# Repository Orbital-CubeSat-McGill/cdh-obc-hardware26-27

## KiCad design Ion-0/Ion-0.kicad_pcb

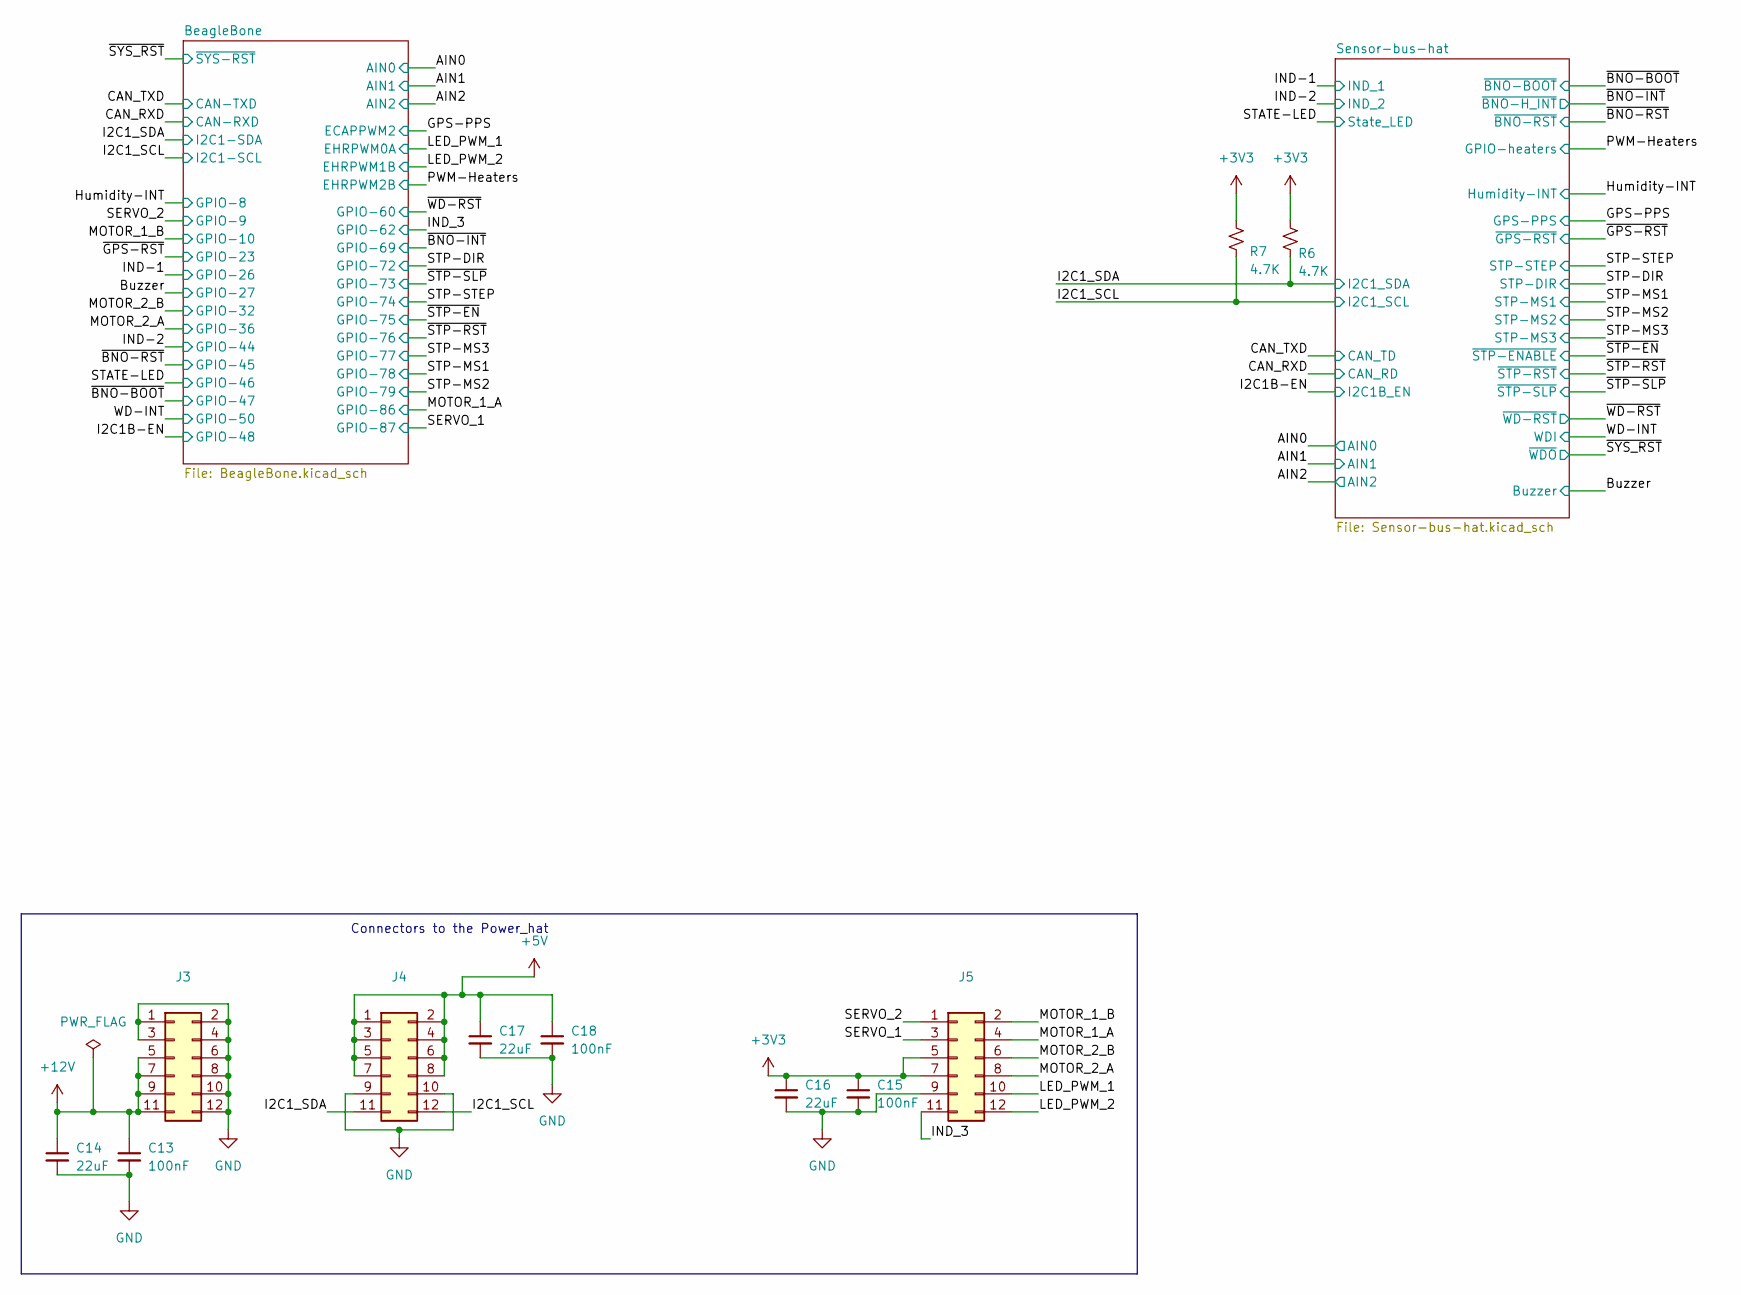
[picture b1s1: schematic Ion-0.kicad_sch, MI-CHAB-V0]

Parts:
C13, C15, C18: 100nF; C_0603_1608Metric
C14, C16, C17: 22uF; C_0603_1608Metric
J3, J4, J5: Conn_02x06_Odd_Even; PinSocket_2x06_P2.54mm_Vertical_SMD
R6, R7: 4.7K; R_0603_1608Metric_Pad0.98x0.95mm_HandSolder

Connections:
+3V3: C15.1, C16.1, J5.5, J5.7, R6.2, R7.1; also elsewhere on the board
+5V: C17.1, C18.1, J4.1, J4.2, J4.3, J4.4, J4.5, J4.6, J4.7, J4.8; also elsewhere on the board
+12V: C13.1, C14.1, J3.5, J3.7, J3.9, J3.11; also elsewhere on the board
/I2C1_SCL: J4.12, R7.2; also elsewhere on the board
/I2C1_SDA: J4.11, R6.1; also elsewhere on the board
/IND_3: J5.11; also elsewhere on the board
/LED_PWM_1: J5.10; also elsewhere on the board
/LED_PWM_2: J5.12; also elsewhere on the board
/MOTOR_1_A: J5.4; also elsewhere on the board
/MOTOR_1_B: J5.2; also elsewhere on the board
/MOTOR_2_A: J5.8; also elsewhere on the board
/MOTOR_2_B: J5.6; also elsewhere on the board
/SERVO_1: J5.3; also elsewhere on the board
/SERVO_2: J5.1; also elsewhere on the board
GND: C13.2, C14.2, C15.2, C16.2, C17.2, C18.2, J3.1, J3.2, J3.3, J3.4, J3.6, J3.8, J3.10, J3.12, J4.9, J4.10, J5.9; also elsewhere on the board

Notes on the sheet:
Connectors to the Power_hat

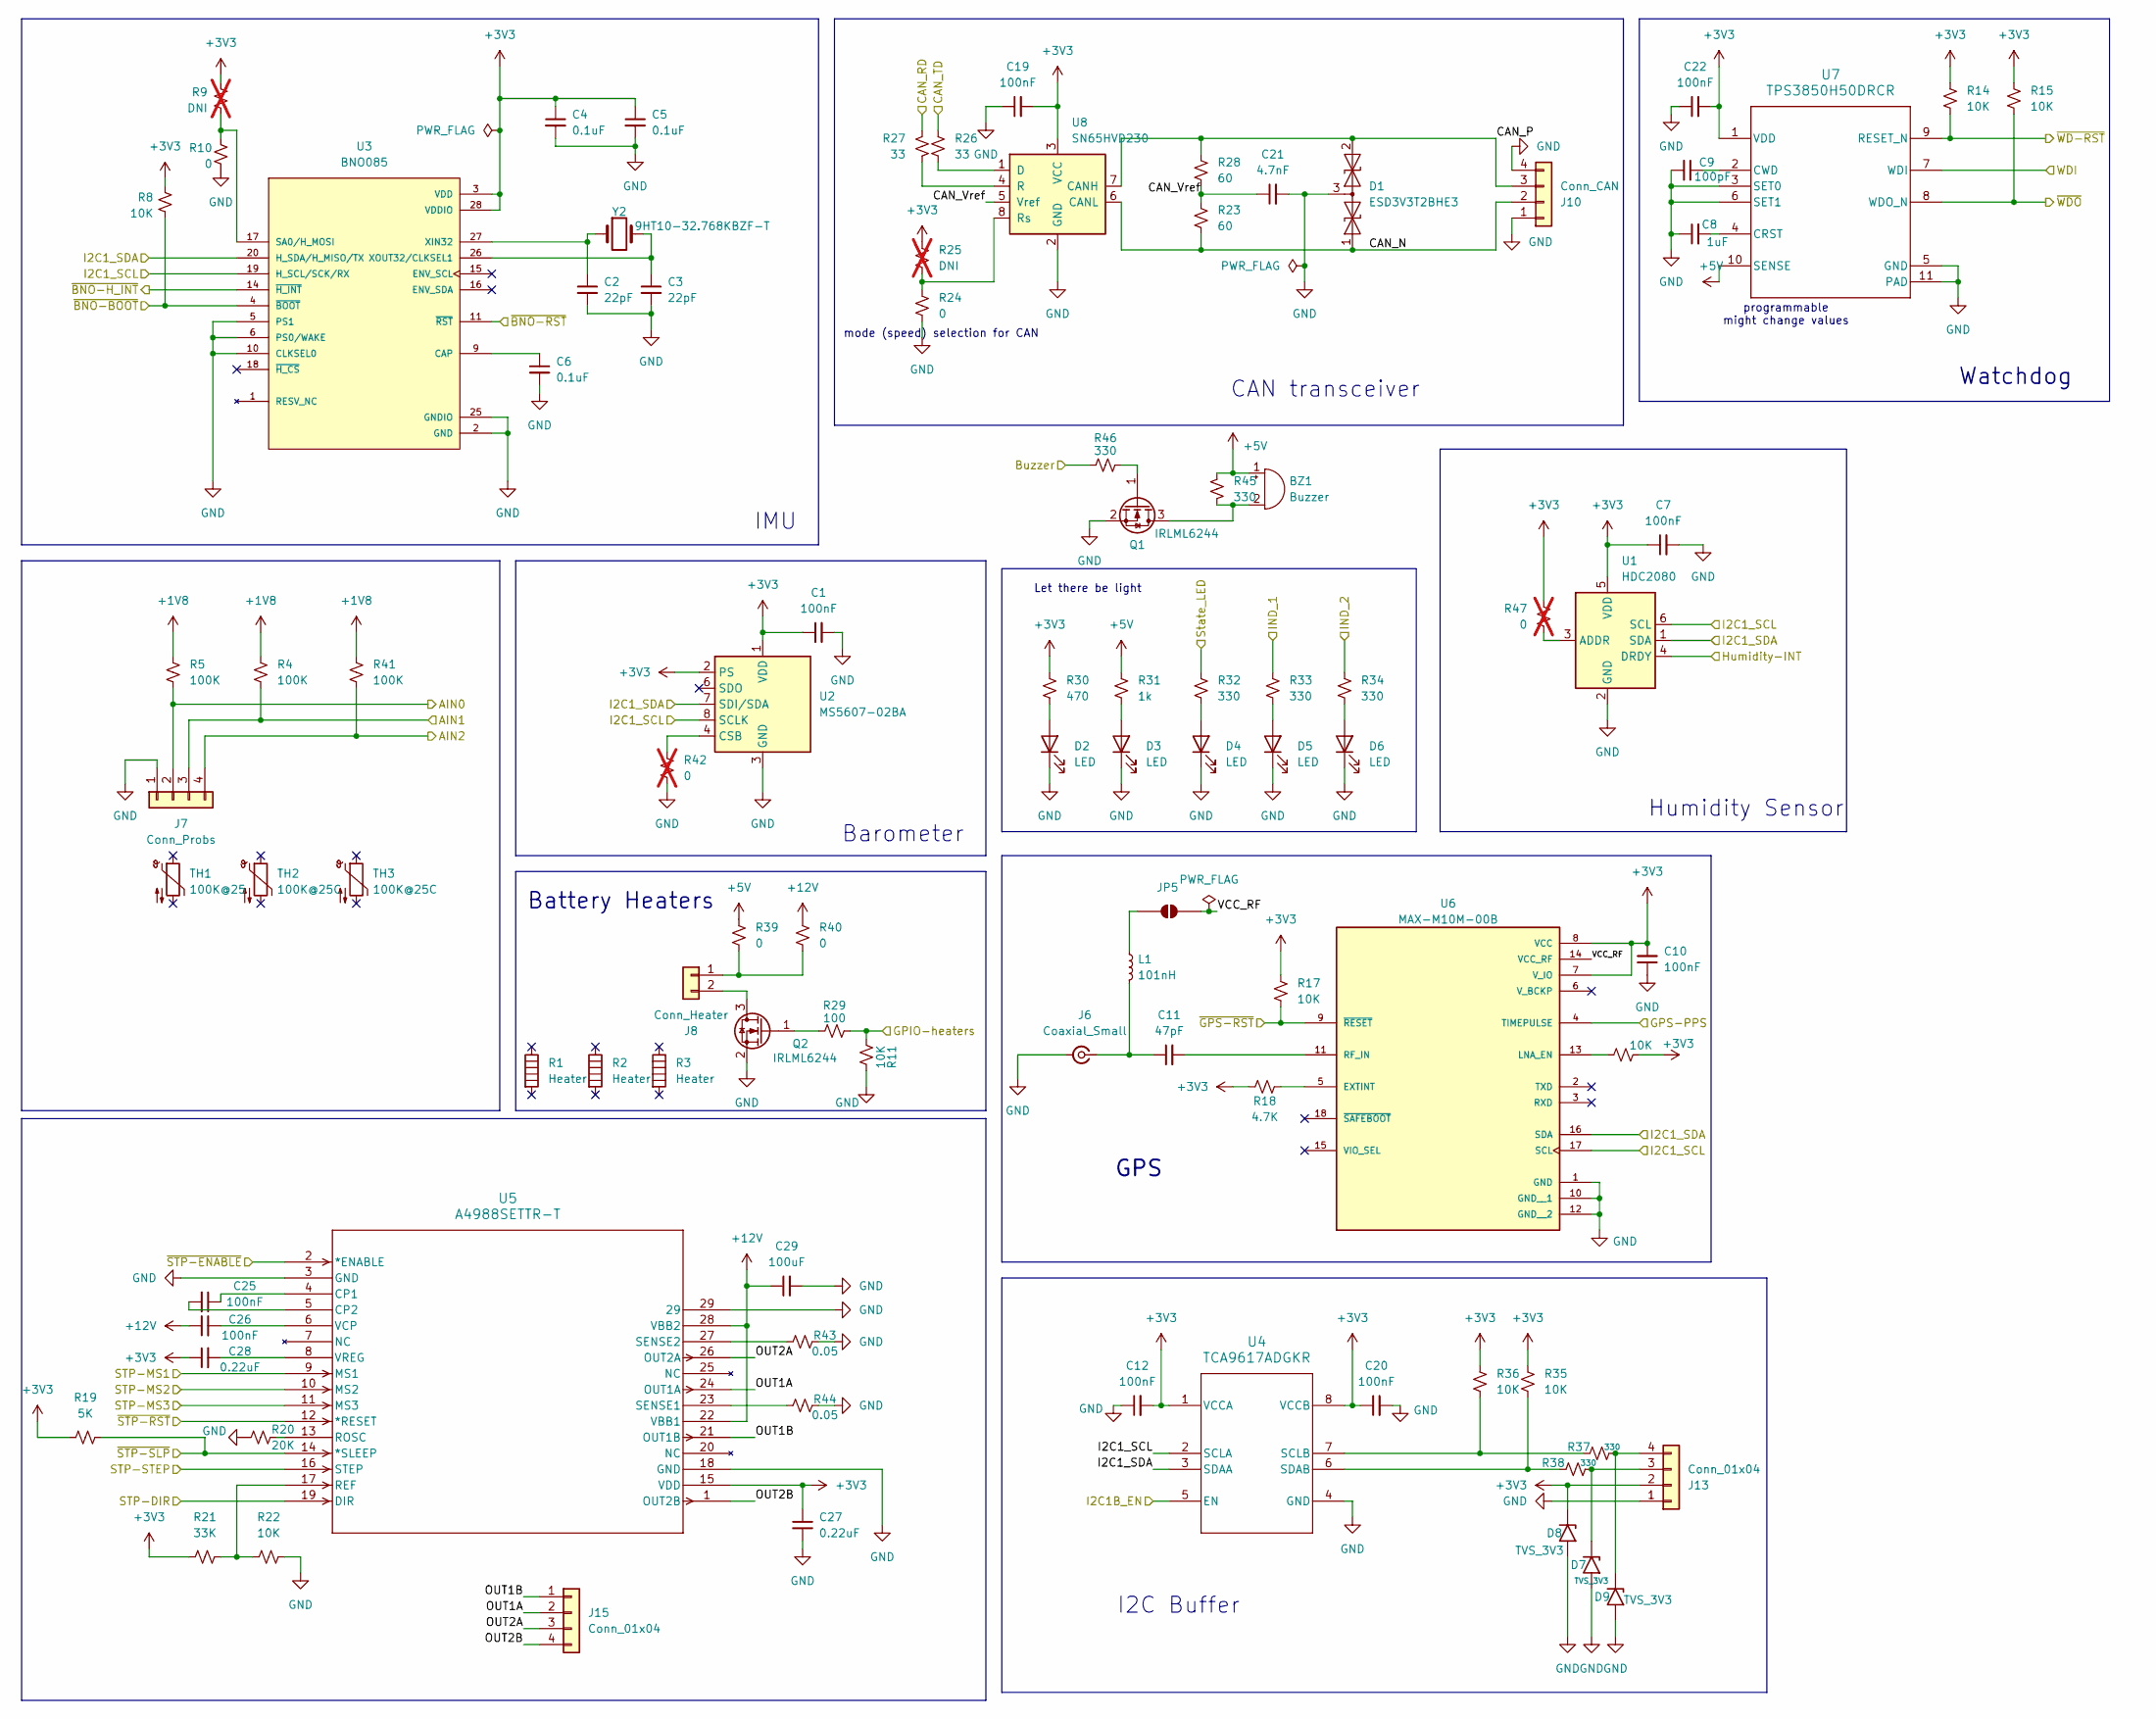
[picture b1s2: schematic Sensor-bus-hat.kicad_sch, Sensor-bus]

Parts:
BZ1: Buzzer; Buzzer_CUI_CPT-9019S-SMT
C1, C7, C10, C12, C19, C20, C22, C25, C26: 100nF; C_0603_1608Metric
C2, C3: 22pF; C_0603_1608Metric
C4, C5, C6: 0.1uF; C_0603_1608Metric
C8: 1uF; C_0603_1608Metric
C9: 100pF; C_0603_1608Metric
C11: 47pF; C_0402_1005Metric
C21: 4.7nF; C_0603_1608Metric
C27, C28: 0.22uF; C_0603_1608Metric
C29: 100uF; C_0603_1608Metric
D1: ESD3V3T2BHE3; SOT-23
D2, D3, D4, D5, D6: LED; LED_0603_1608Metric_Pad1.05x0.95mm_HandSolder
D7, D8, D9: TVS_3V3; D_0603_1608Metric
J6: Coaxial_Small; U.FL_Molex_MCRF_73412-0110_Vertical
J7: Conn_Probs; TerminalBlock_Xinya_XY308-2.54-4P_1x04_P2.54mm_Horizontal
J8: Conn_Heater; TerminalBlock_Xinya_XY308-2.54-2P_1x02_P2.54mm_Horizontal
J10: Conn_CAN; JST_SH_SM04B-SRSS-TB_1x04-1MP_P1.00mm_Horizontal
J13: Conn_01x04; JST_SH_SM04B-SRSS-TB_1x04-1MP_P1.00mm_Horizontal
J15: Conn_01x04; TerminalBlock_Xinya_XY308-2.54-4P_1x04_P2.54mm_Horizontal
JP5: SolderJumper_2_Open; SolderJumper-2_P1.3mm_Open_TrianglePad1.0x1.5mm
L1: 101nH; L_0402_1005Metric
Q1, Q2: IRLML6244; SOT-23
R1, R2, R3: Heater
R4, R5, R41: 100K; R_0603_1608Metric_Pad0.98x0.95mm_HandSolder
R8, R11, R14, R15, R16, R17, R22, R35, R36: 10K; R_0603_1608Metric_Pad0.98x0.95mm_HandSolder
R9, R25: DNI; R_0603_1608Metric_Pad0.98x0.95mm_HandSolder; not fitted
R10, R24: 0; R_0603_1608Metric_Pad0.98x0.95mm_HandSolder
R18: 4.7K; R_0603_1608Metric_Pad0.98x0.95mm_HandSolder
R19: 5K; R_0603_1608Metric_Pad0.98x0.95mm_HandSolder
R20: 20K; R_0603_1608Metric_Pad0.98x0.95mm_HandSolder
R21: 33K; R_0603_1608Metric_Pad0.98x0.95mm_HandSolder
R23, R28: 60; R_0603_1608Metric_Pad0.98x0.95mm_HandSolder
R26, R27: 33; R_0603_1608Metric_Pad0.98x0.95mm_HandSolder
R29: 100; R_0603_1608Metric_Pad0.98x0.95mm_HandSolder
R30: 470; R_0603_1608Metric_Pad0.98x0.95mm_HandSolder
R31: 1k; R_0603_1608Metric_Pad0.98x0.95mm_HandSolder
R32, R33, R34, R37, R38, R45, R46: 330; R_0603_1608Metric_Pad0.98x0.95mm_HandSolder
R39, R40: 0; R_1206_3216Metric
R42, R47: 0; R_0603_1608Metric_Pad0.98x0.95mm_HandSolder; not fitted
R43, R44: 0.05; R_0603_1608Metric_Pad0.98x0.95mm_HandSolder
TH1: 100K@25
TH2, TH3: 100K@25C
U1: HDC2080; Texas_S-PWSON-N6-HDC2080
U2: MS5607-02BA; LGA-8_3x5mm_P1.25mm
U3: BNO085; IC_BNO085; PARTREV v1.17
U4: TCA9617ADGKR; TCA9617A
U5: A4988SETTR-T; QFN-28_ALM
U6: MAX-M10M-00B; XCVR_MAX-M10M-00B; PARTREV C1
U7: TPS3850H50DRCR; TPS3850
U8: SN65HVD230; SOIC-8_3.9x4.9mm_P1.27mm
Y2: 9HT10-32.768KBZF-T; L_1206_3216Metric

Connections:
+1V8: R4.1, R5.1, R41.1; also elsewhere on the board
+3V3: C1.1, C4.1, C5.1, C7.1, C10.2, C12.2, C19.2, C20.1, C22.2, C27.1, C28.1, D8.1 (A1), J13.2, R8.1, R9.1, R14.1, R15.1, R16.2, R17.1, R18.2, R19.2, R21.1, R25.1, R30.1, R35.1, R36.1, R47.1, U1.5 (VDD), U2.1 (VDD), U2.2 (PS), U3.3 (VDD), U3.28 (VDDIO), U4.1 (VCCA), U4.8 (VCCB), U5.15 (VDD), U6.7 (V_IO), U6.8 (VCC), U7.1 (VDD), U8.3 (VCC); also elsewhere on the board
+5V: BZ1.1 (+), R31.1, R39.1, R45.1, U7.10 (SENSE); also elsewhere on the board
+12V: C26.1, C29.1, R40.1, U5.22 (VBB1), U5.28 (VBB2); also elsewhere on the board
/AIN0: J7.2, R5.2; also elsewhere on the board
/AIN1: J7.3, R4.2; also elsewhere on the board
/AIN2: J7.4, R41.2; also elsewhere on the board
/Buzzer: R46.1; also elsewhere on the board
/CAN_RXD: R27.1; also elsewhere on the board
/CAN_TXD: R26.1; also elsewhere on the board
/GPS-PPS: U6.4 (TIMEPULSE); also elsewhere on the board
/Humidity-INT: U1.4 (DRDY); also elsewhere on the board
/I2C1B-EN: U4.5 (EN); also elsewhere on the board
/I2C1_SCL: U1.6 (SCL), U2.8 (SCLK), U3.19 (H_SCL/SCK/RX), U4.2 (SCLA), U6.17 (SCL); also elsewhere on the board
/I2C1_SDA: U1.1 (SDA), U2.7 (SDI/SDA), U3.20 (H_SDA/H_MISO/TX), U4.3 (SDAA), U6.16 (SDA); also elsewhere on the board
/IND-1: R33.1; also elsewhere on the board
/IND-2: R34.1; also elsewhere on the board
/PWM-Heaters: R11.1, R29.1; also elsewhere on the board
/STATE-LED: R32.1; also elsewhere on the board
/STP-DIR: U5.19 (DIR); also elsewhere on the board
/STP-MS1: U5.9 (MS1); also elsewhere on the board
/STP-MS2: U5.10 (MS2); also elsewhere on the board
/STP-MS3: U5.11 (MS3); also elsewhere on the board
/STP-STEP: U5.16 (STEP); also elsewhere on the board
/Sensor-bus-hat/CAN_N: D1.1 (A1), J10.2, R23.2, U8.6 (CANL)
/Sensor-bus-hat/CAN_P: D1.2 (A2), J10.3, R28.1, U8.7 (CANH)
/Sensor-bus-hat/CAN_Vref: C21.1, R23.1, R28.2, U8.5 (Vref)
/Sensor-bus-hat/OUT1A: J15.2, U5.24 (OUT1A)
/Sensor-bus-hat/OUT1B: J15.1, U5.21 (OUT1B)
/Sensor-bus-hat/OUT2A: J15.3, U5.26 (OUT2A)
/Sensor-bus-hat/OUT2B: J15.4, U5.1 (OUT2B)
/Sensor-bus-hat/VCC_RF: JP5.2 (B), U6.14 (VCC_RF)
/WD-INT: U7.7 (WDI); also elsewhere on the board
/~BNO-BOOT: R8.2, U3.4 (~BOOT); also elsewhere on the board
/~BNO-INT: U3.14 (~H_INT); also elsewhere on the board
/~BNO-RST: U3.11 (~RST); also elsewhere on the board
/~GPS-RST: R17.2, U6.9 (~RESET); also elsewhere on the board
/~STP-EN: U5.2 (*ENABLE); also elsewhere on the board
/~STP-RST: U5.12 (*RESET); also elsewhere on the board
/~STP-SLP: R19.1, U5.14 (*SLEEP); also elsewhere on the board
/~SYS_RST: R15.2, U7.8 (WDO_N); also elsewhere on the board
/~WD-RST: R14.2, U7.9 (RESET_N); also elsewhere on the board
GND: C1.2, C2.2, C3.2, C4.2, C5.2, C6.2, C7.2, C8.1, C9.2, C10.1, C12.1, C19.1, C20.2, C21.2, C22.1, C27.2, C29.2, D1.3 (common), D2.1 (K), D3.1 (K), D4.1 (K), D5.1 (K), D6.1 (K), D7.2 (A2), D8.2 (A2), D9.2 (A2), J6.2 (Ext), J7.1, J10.1, J10.4, J13.1, Q1.2 (S), Q2.2 (S), R10.2, R11.2, R20.1, R22.2, R24.2, R42.2, R43.2, R44.2, U1.2 (GND), U2.3 (GND), U3.2 (GND), U3.5 (PS1), U3.6 (PS0/WAKE), U3.10 (CLKSEL0), U3.25 (GNDIO), U4.4 (GND), U5.3 (GND), U5.18 (GND), U5.29, U6.1 (GND), U6.10 (GND__1), U6.12 (GND__2), U7.3 (SET0), U7.5 (GND), U7.6 (SET1), U7.11 (PAD), U8.2 (GND); also elsewhere on the board
unnamed: BZ1.2 (-), Q1.3 (D), R45.2
unnamed: D2.2 (A), R30.2
unnamed: D3.2 (A), R31.2
unnamed: D4.2 (A), R32.2
unnamed: D5.2 (A), R33.2
unnamed: D6.2 (A), R34.2
unnamed: D7.1 (A1), J13.3, R38.2
unnamed: D9.1 (A1), J13.4, R37.2
unnamed: C11.1, J6.1 (In), L1.2
unnamed: J8.1, R39.2, R40.2
unnamed: J8.2, Q2.3 (D)
unnamed: JP5.1 (A), L1.1
unnamed: Q1.1 (G), R46.2
unnamed: Q2.1 (G), R29.2
unnamed: R42.1, U2.4 (CSB), U2.5 (CSB)
unnamed: R47.2, U1.3 (ADDR)
unnamed: C6.1, U3.9 (CAP)
unnamed: R9.2, R10.1, U3.17 (SA0/H_MOSI)
unnamed: C2.1, U3.27 (XIN32), Y2.1
unnamed: C3.1, U3.26 (XOUT32/CLKSEL1), Y2.2
unnamed: R36.2, R37.1, U4.7 (SCLB)
unnamed: R35.2, R38.1, U4.6 (SDAB)
unnamed: C25.1, U5.4 (CP1)
unnamed: C25.2, U5.5 (CP2)
unnamed: R21.2, R22.1, U5.17 (REF)
unnamed: R20.2, U5.13 (ROSC)
unnamed: R44.1, U5.23 (SENSE1)
unnamed: R43.1, U5.27 (SENSE2)
unnamed: C26.2, U5.6 (VCP)
unnamed: C28.2, U5.8 (VREG)
unnamed: R18.1, U6.5 (EXTINT)
unnamed: R16.1, U6.13 (LNA_EN)
unnamed: C11.2, U6.11 (RF_IN)
unnamed: C8.2, U7.4 (CRST)
unnamed: C9.1, U7.2 (CWD)
unnamed: R26.2, U8.1 (D)
unnamed: R27.2, U8.4 (R)
unnamed: R24.1, R25.2, U8.8 (Rs)

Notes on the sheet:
Barometer
Humidity Sensor
Watchdog
IMU
Let there be light
CAN transceiver
programmable might change values
GPS
I2C Buffer
mode (speed) selection for CAN
Battery Heaters

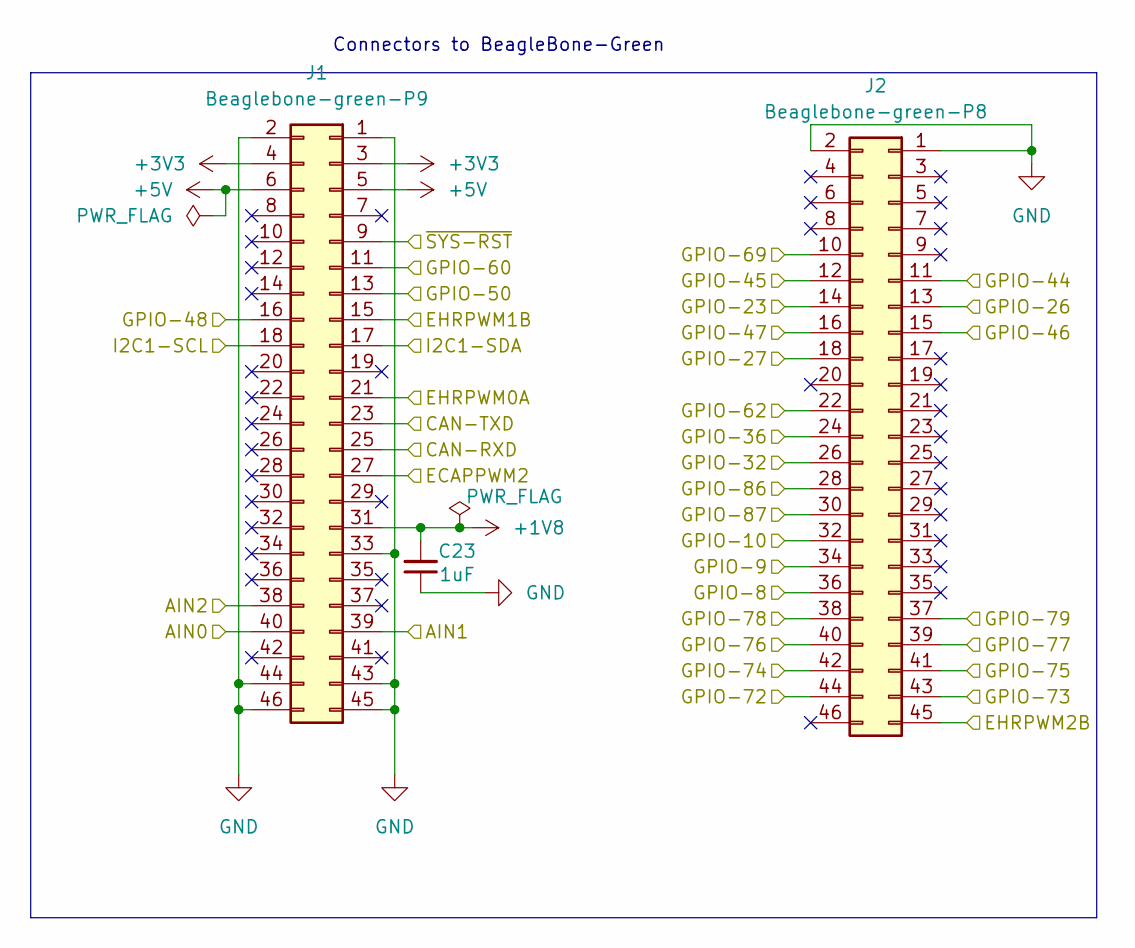
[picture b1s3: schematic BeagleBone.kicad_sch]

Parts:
C23: 1uF; C_0603_1608Metric
J1: Beaglebone-green-P9; PinHeader_2x23_P2.54mm_Vertical
J2: Beaglebone-green-P8; PinHeader_2x23_P2.54mm_Vertical

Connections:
+1V8: C23.2, J1.31; also elsewhere on the board
+3V3: J1.3, J1.4; also elsewhere on the board
+5V: J1.5, J1.6; also elsewhere on the board
/AIN0: J1.40; also elsewhere on the board
/AIN1: J1.39; also elsewhere on the board
/AIN2: J1.38; also elsewhere on the board
/Buzzer: J2.18; also elsewhere on the board
/CAN_RXD: J1.25; also elsewhere on the board
/CAN_TXD: J1.23; also elsewhere on the board
/GPS-PPS: J1.27; also elsewhere on the board
/Humidity-INT: J2.36; also elsewhere on the board
/I2C1B-EN: J1.16; also elsewhere on the board
/I2C1_SCL: J1.18; also elsewhere on the board
/I2C1_SDA: J1.17; also elsewhere on the board
/IND-1: J2.13; also elsewhere on the board
/IND-2: J2.11; also elsewhere on the board
/IND_3: J2.22; also elsewhere on the board
/LED_PWM_1: J1.21; also elsewhere on the board
/LED_PWM_2: J1.15; also elsewhere on the board
/MOTOR_1_A: J2.28; also elsewhere on the board
/MOTOR_1_B: J2.32; also elsewhere on the board
/MOTOR_2_A: J2.24; also elsewhere on the board
/MOTOR_2_B: J2.26; also elsewhere on the board
/PWM-Heaters: J2.45; also elsewhere on the board
/SERVO_1: J2.30; also elsewhere on the board
/SERVO_2: J2.34; also elsewhere on the board
/STATE-LED: J2.15; also elsewhere on the board
/STP-DIR: J2.44; also elsewhere on the board
/STP-MS1: J2.38; also elsewhere on the board
/STP-MS2: J2.37; also elsewhere on the board
/STP-MS3: J2.39; also elsewhere on the board
/STP-STEP: J2.42; also elsewhere on the board
/WD-INT: J1.13; also elsewhere on the board
/~BNO-BOOT: J2.16; also elsewhere on the board
/~BNO-INT: J2.10; also elsewhere on the board
/~BNO-RST: J2.12; also elsewhere on the board
/~GPS-RST: J2.14; also elsewhere on the board
/~STP-EN: J2.41; also elsewhere on the board
/~STP-RST: J2.40; also elsewhere on the board
/~STP-SLP: J2.43; also elsewhere on the board
/~SYS_RST: J1.9; also elsewhere on the board
/~WD-RST: J1.11; also elsewhere on the board
GND: C23.1, J1.1, J1.2, J1.33, J1.43, J1.44, J1.45, J1.46, J2.1, J2.2; also elsewhere on the board

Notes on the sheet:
Connectors to BeagleBone-Green

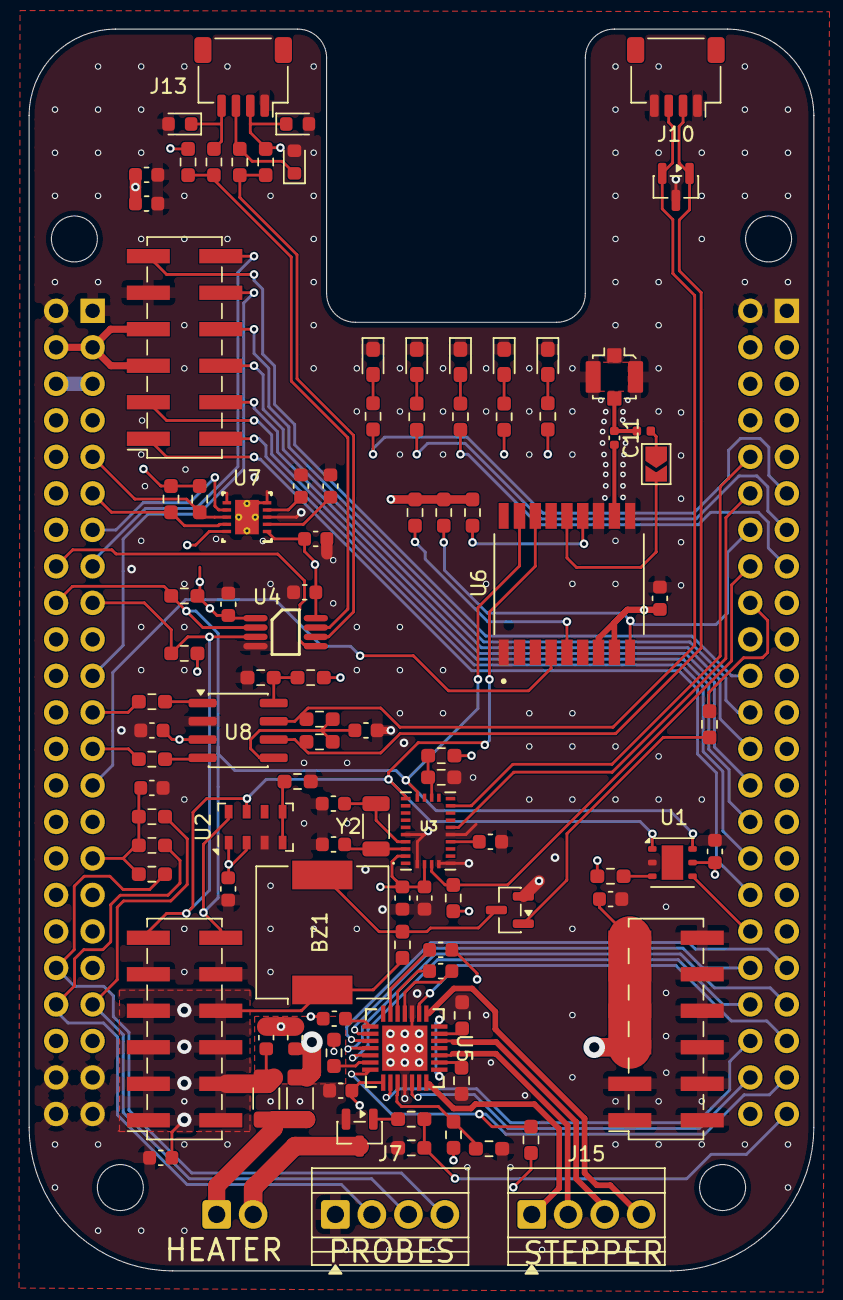
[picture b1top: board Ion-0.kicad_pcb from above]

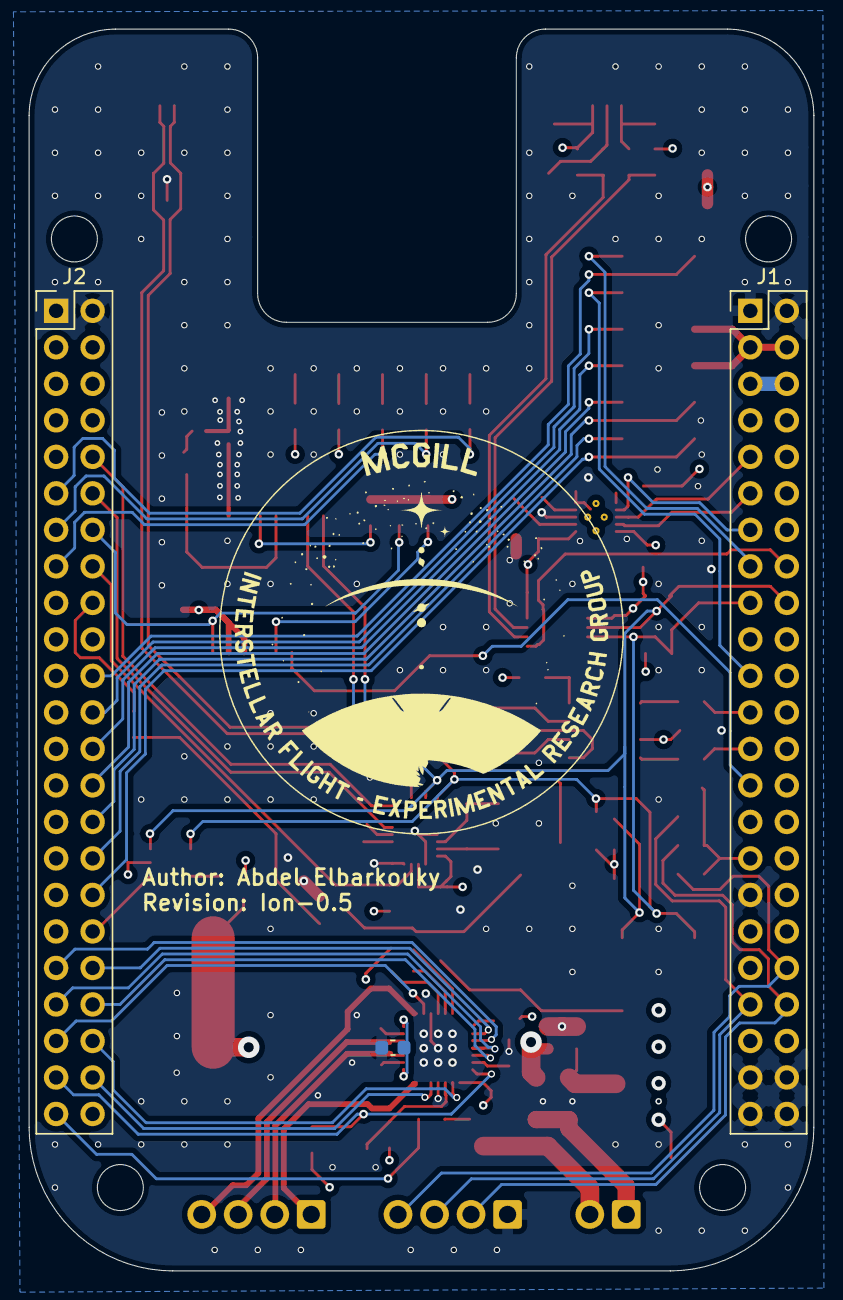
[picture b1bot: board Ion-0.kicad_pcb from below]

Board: 4 copper layers, 54.6 x 86.4 mm, 104 parts (3 on the bottom side), 90 nets.

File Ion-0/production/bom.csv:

Designator,Footprint,Quantity,Value,LCSC Part #
BZ1,Buzzer_CUI_CPT-9019S-SMT,1,Buzzer,C95163
"C1, C10, C12, C13, C15, C18, C19, C20, C22, C25, C26, C7",0603,12,100nF,C16194197
C11,0402,1,47pF,C76970
"C14, C16, C17",0603,3,22uF,C602037
"C2, C3",0603,2,22pF,C408549
C21,0603,1,4.7nF,C1621
"C23, C8",0603,2,1uF,C5199872
"C27, C28",0603,2,0.22uF,C2167136
C29,0603,1,100uF,C48970603
"C4, C5, C6",0603,3,0.1uF,
C9,0603,1,100pF,C14665
D1,SOT-23,1,ESD3V3T2BHE3,C1973960
"D2, D3, D4, D5, D6",0603,5,LED,C125093
"D7, D8, D9",0603,3,TVS_3V3,C2693608
J1,PinHeader_2x23_P2.54mm_Vertical,1,Beaglebone-green-P9,C7501270
J10,JST_SH_SM04B-SRSS-TB_1x04-1MP_P1.00mm_Horizontal,1,Conn_CAN,C160404
J13,JST_SH_SM04B-SRSS-TB_1x04-1MP_P1.00mm_Horizontal,1,Conn_01x04,C160404
J15,TerminalBlock_Xinya_XY308-2.54-4P_1x04_P2.54mm_Horizontal,1,Conn_01x04,
J2,PinHeader_2x23_P2.54mm_Vertical,1,Beaglebone-green-P8,C7501270
"J3, J4, J5",PinSocket_2x06_P2.54mm_Vertical_SMD,3,Conn_02x06_Odd_Even,C7501277
J6,U.FL_Molex_MCRF_73412-0110_Vertical,1,Coaxial_Small,C88373
J7,TerminalBlock_Xinya_XY308-2.54-4P_1x04_P2.54mm_Horizontal,1,Conn_Probs,
J8,TerminalBlock_Xinya_XY308-2.54-2P_1x02_P2.54mm_Horizontal,1,Conn_Heater,
L1,0402,1,101nH,C86130
"Q1, Q2",SOT-23,2,IRLML6244,C5364311
"R10, R24, R42, R47",0603,4,0,C95177
"R11, R14, R15, R16, R17, R22, R35, R36, R8",0603,9,10K,C98220
"R18, R6, R7",0603,3,4.7K,C99782
R19,0603,1,5K,C862232
R20,0603,1,20K,C190611
R21,0603,1,33K,C4009252
"R23, R28",0603,2,60,C4110481
"R25, R9",0603,2,DNI,
"R26, R27",0603,2,33,C108661
R29,0603,1,100,C105588
R30,0603,1,470,C666997
R31,0603,1,1k,C22548
"R32, R33, R34, R37, R38, R45, R46",0603,7,330,C105879
"R39, R40",1206,2,0,C22468037
"R4, R41, R5",0603,3,100K,C14675
"R43, R44",0603,2,0.05,C346483
U1,Texas_S-PWSON-N6-HDC2080,1,HDC2080,C918141
U2,LGA-8_3x5mm_P1.25mm,1,MS5607-02BA,C97627
U3,IC_BNO085,1,BNO085,
U4,TCA9617A,1,TCA9617ADGKR,C400707
U5,QFN-28_ALM,1,A4988SETTR-T,C54823939
U6,XCVR_MAX-M10M-00B,1,MAX-M10M-00B,C4153167
U7,TPS3850,1,TPS3850H50DRCR,C2066856
U8,SOIC-8_3.9x4.9mm_P1.27mm,1,SN65HVD230,C12084
Y2,1206,1,9HT10-32.768KBZF-T,C32346
